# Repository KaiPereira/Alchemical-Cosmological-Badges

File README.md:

# Alchemical-Cosmological Badges

These are alchemical-cosmological PCB hackathon badges I designed in a day for the Fallout hackathon in Shenzhen, China. It's 3 PCB's stacked on-top of each other using testpoints and it's powered by the 10 cent, CH32V003 MCU, with WS2812B neopixels.

## PCB Design

There's 2 different PCB's: the outer ring and the inner sun. The 2 outer rings are soldered onto the testpoints of the inner one with the second outer ring rotated 180 degree's to look more 3D.

The rings have exposed soldermask so that the neopixels can shine through, and you actually only need to solder neopixels onto one ring to get the effect.

There's also a battery connector on the top-left corner to attach a small battery with a voltage between 2.7V - 5V, and I'd just suggest a small LiPo, that can potentially even slot in-between the boards.

I'd also suggest putting a hole for your lanyard, because currently I just have a string wrapped around the board which looks cool, but isn't the most convenient for assembly. 

## Manufacturing

Each full badge costs about $10 at MOQ, but I'm sure you could get that down to under $3 if you create quite a few at once.

If you want to manufacture the boards, all of their production and development files are in their relative folder. I'd suggest getting the boards from JLCPCB with ENIG and a stencil for the inner board, and then buying the components from LCSC and hand soldering. 

All the design files are also open-source if you want to make modifications so that they're unique to you, so just go crazy!!

These boards were designed really fast and made to be really cheap because of a limited budget, so produce them at your own discretion.

## Firmware

These boards use the CH32V003 and program over SWIO using the header pins in the middle of the board. You'll want to program the boards using either a WCH-LinkE or PicoRVD which is what I used and what you'll find in the firmware folder.

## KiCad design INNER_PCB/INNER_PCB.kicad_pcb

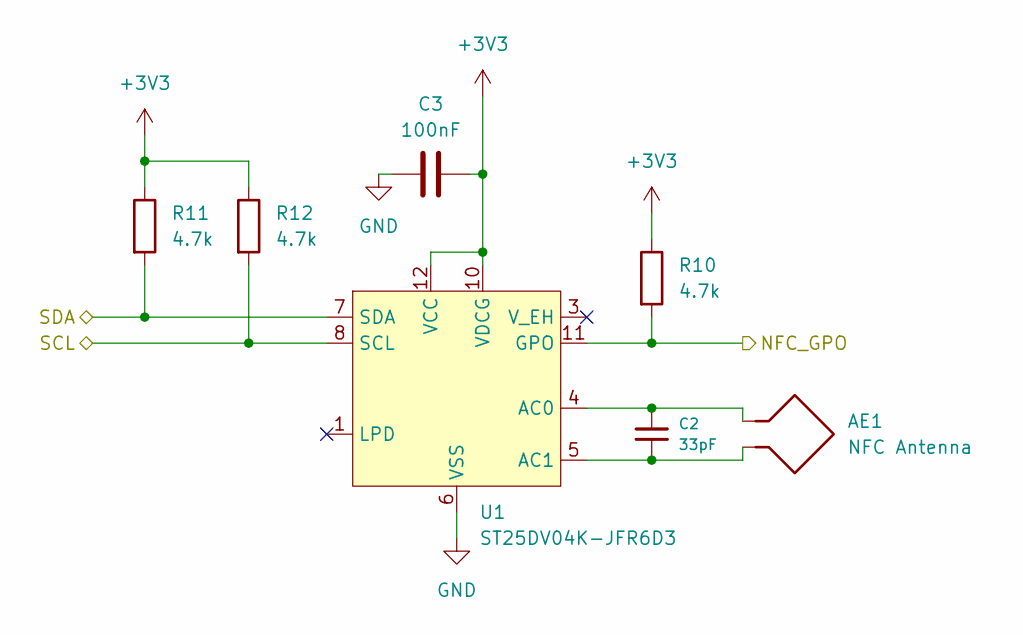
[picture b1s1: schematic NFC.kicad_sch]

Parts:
AE1: NFC Antenna; NFC_Coil_Round_D20mm_17T
C2: 33pF; C_0603_1608Metric; JLCPCB Part # C1663
C3: 100nF; C_0603_1608Metric; JLCPCB Part # C14663
R10, R11, R12: 4.7k; R_0603_1608Metric; JLCPCB Part # C23162
U1: ST25DV04K-JFR6D3; ST_UFDFPN-12-1EP_3x3mm_P0.5mm_EP1.4x2.55mm; JLCPCB Part # C2654815

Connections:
+3V3: C3.2, R10.1, R11.1, R12.1, U1.10 (VDCG), U1.12 (VCC); also elsewhere on the board
/MCU, Programming and Battery/NFC_GPO: R10.2, U1.11 (GPO); also elsewhere on the board
/MCU, Programming and Battery/SCL: R12.2, U1.8 (SCL); also elsewhere on the board
/MCU, Programming and Battery/SDA: R11.2, U1.7 (SDA); also elsewhere on the board
GND: C3.1, U1.6 (VSS); also elsewhere on the board
unnamed: AE1.1, C2.1, U1.4 (AC0)
unnamed: AE1.2, C2.2, U1.5 (AC1)

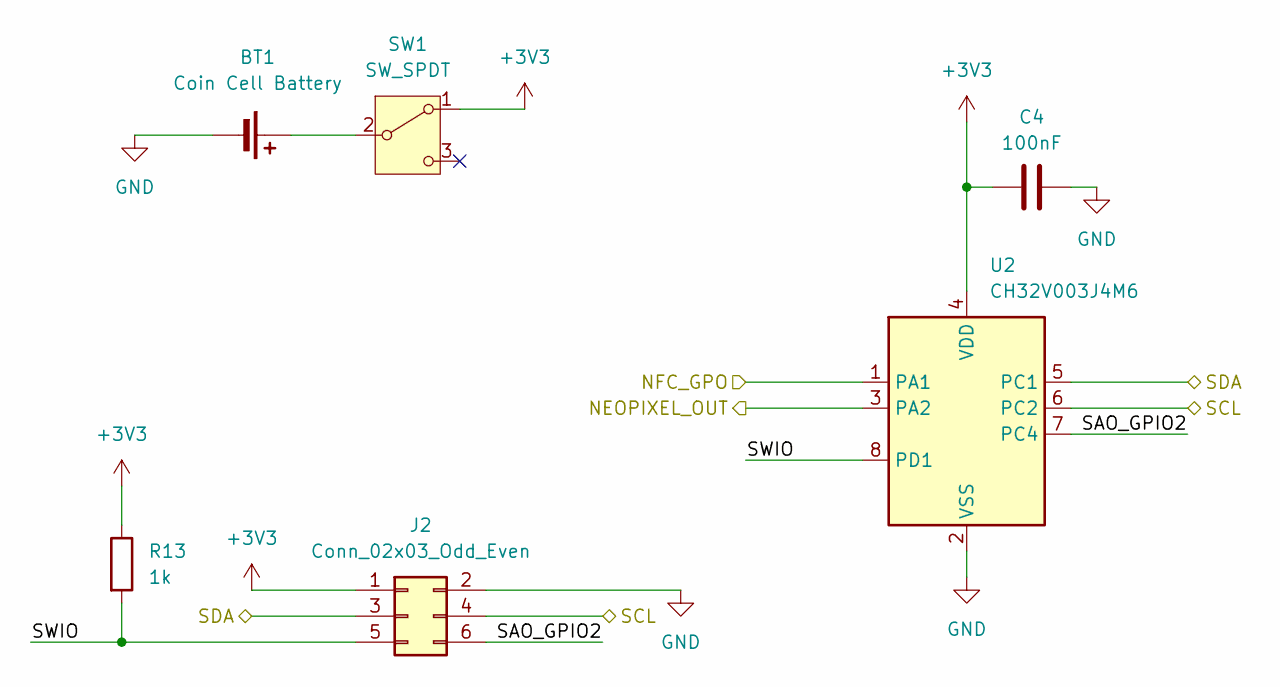
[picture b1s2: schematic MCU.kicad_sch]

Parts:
BT1: Coin Cell Battery; BatteryHolder_Keystone_1058_1x2032; JLCPCB Part # C964769
C4: 100nF; C_0603_1608Metric; JLCPCB Part # C14663
J2: Conn_02x03_Odd_Even; PinHeader_2x03_P2.54mm_Vertical_SMD; JLCPCB Part # C192301
R13: 1k; R_0603_1608Metric; JLCPCB Part # C21190
SW1: SW_SPDT; SS-3292S-L1-B; JLCPCB Part # C397350
U2: CH32V003J4M6; SSOP-8_3.9x5.05mm_P1.27mm; LCSC Part # C5346354

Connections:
+3V3: C4.1, J2.1, R13.1, SW1.1 (A), U2.4 (VDD); also elsewhere on the board
/Connecting Solder Points/NEOPIXEL_IN: U2.3 (PA2); also elsewhere on the board
/MCU, Programming and Battery/NFC_GPO: U2.1 (PA1); also elsewhere on the board
/MCU, Programming and Battery/SAO_GPIO2: J2.6, U2.7 (PC4)
/MCU, Programming and Battery/SCL: J2.4, U2.6 (PC2); also elsewhere on the board
/MCU, Programming and Battery/SDA: J2.3, U2.5 (PC1); also elsewhere on the board
/MCU, Programming and Battery/SWIO: J2.5, R13.2, U2.8 (PD1)
GND: BT1.2 (-), C4.2, J2.2, U2.2 (VSS); also elsewhere on the board
unnamed: BT1.1 (+), SW1.2 (B)

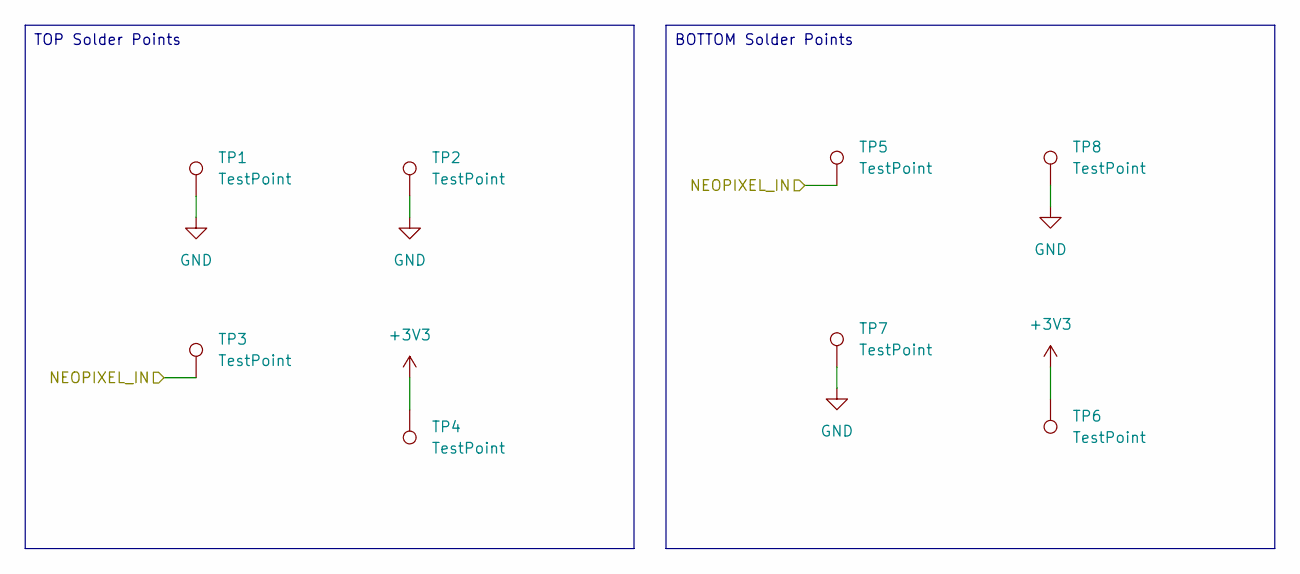
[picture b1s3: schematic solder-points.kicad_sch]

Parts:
TP1, TP2, TP3, TP4, TP5, TP6, TP7, TP8: TestPoint; TestPoint_Pad_3.0x3.0mm

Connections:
+3V3: TP4.1 (1_1), TP6.1 (1_1); also elsewhere on the board
/Connecting Solder Points/NEOPIXEL_IN: TP3.1 (1_1), TP5.1 (1_1); also elsewhere on the board
GND: TP1.1 (1_1), TP2.1 (1_1), TP7.1 (1_1), TP8.1 (1_1); also elsewhere on the board

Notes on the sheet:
TOP Solder Points
BOTTOM Solder Points

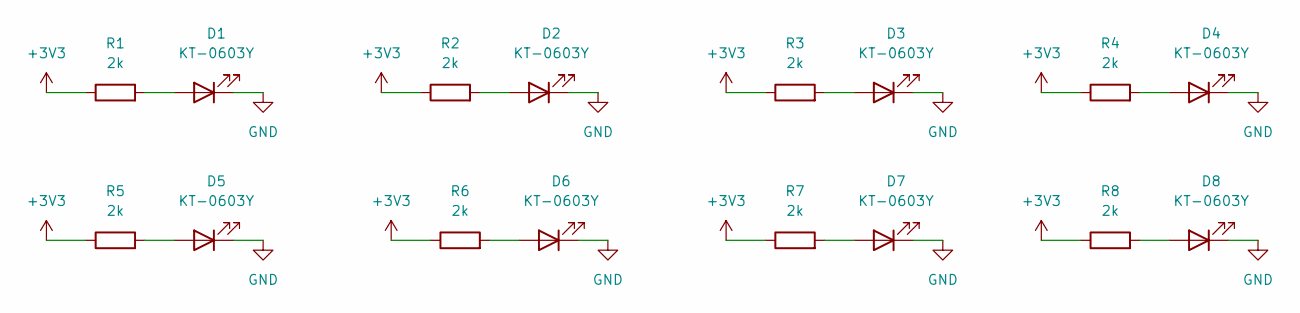
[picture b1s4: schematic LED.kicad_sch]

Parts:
D1, D2, D3, D4, D5, D6, D7, D8: KT-0603Y; LED_0603_1608Metric; JLCPCB Part # C2287
R1, R2, R3, R4, R5, R6, R7, R8: 2k; R_0402_1005Metric; JLCPCB Part # C4109

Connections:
+3V3: R1.1, R2.1, R3.1, R4.1, R5.1, R6.1, R7.1, R8.1; also elsewhere on the board
GND: D1.1 (K), D2.1 (K), D3.1 (K), D4.1 (K), D5.1 (K), D6.1 (K), D7.1 (K), D8.1 (K); also elsewhere on the board
unnamed: D1.2 (A), R1.2
unnamed: D2.2 (A), R2.2
unnamed: D3.2 (A), R3.2
unnamed: D4.2 (A), R4.2
unnamed: D5.2 (A), R5.2
unnamed: D6.2 (A), R6.2
unnamed: D7.2 (A), R7.2
unnamed: D8.2 (A), R8.2

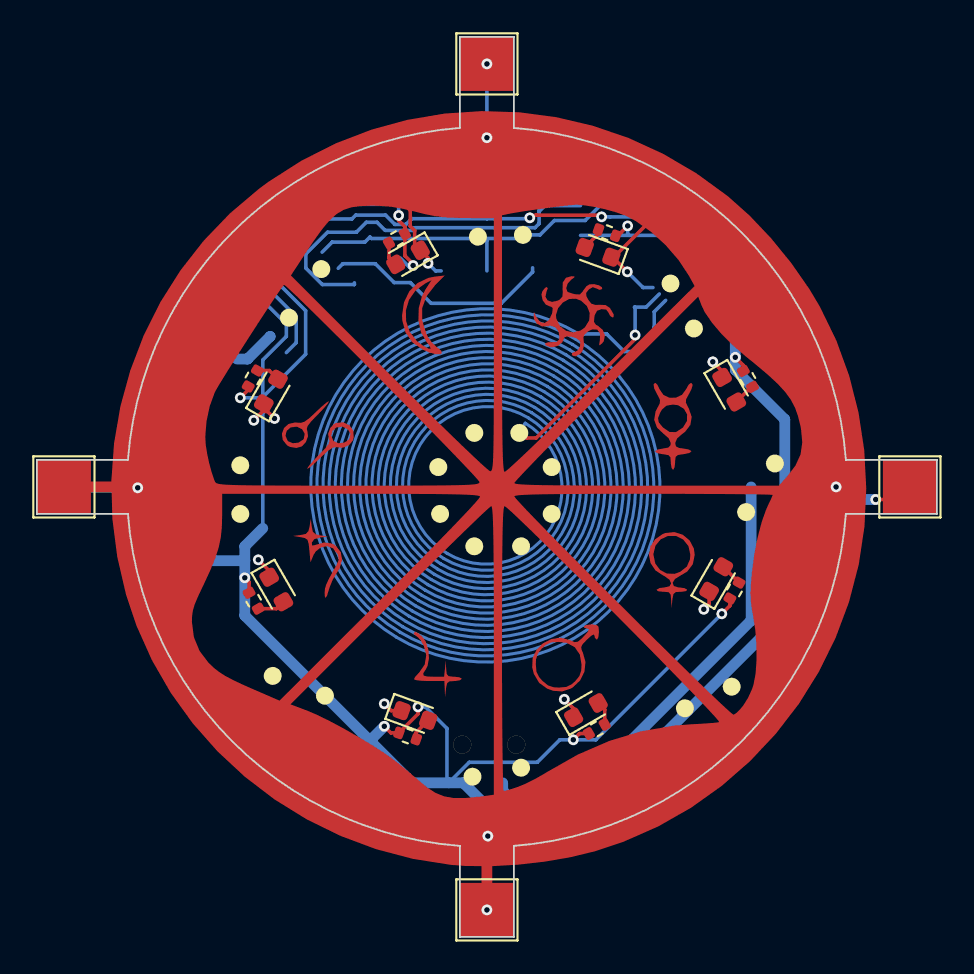
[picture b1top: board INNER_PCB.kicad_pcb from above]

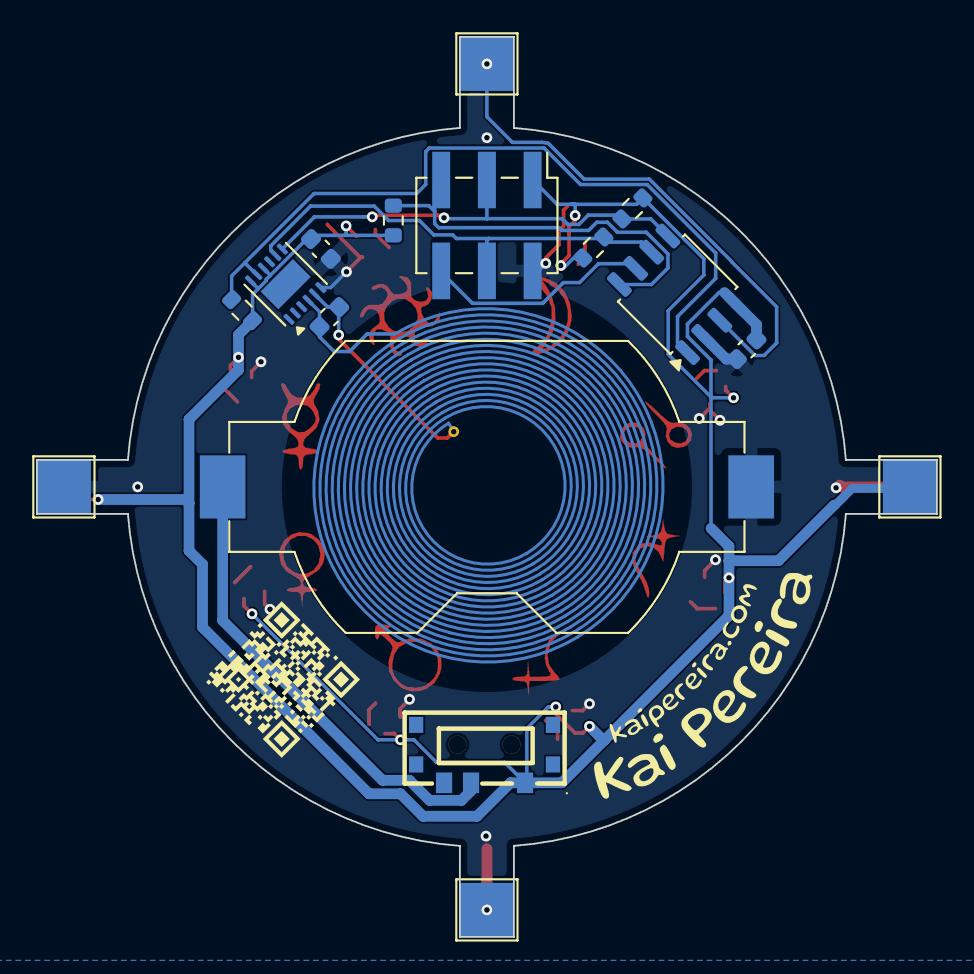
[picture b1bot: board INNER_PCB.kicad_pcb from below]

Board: 2 copper layers, 50.0 x 50.0 mm, 37 parts (17 on the bottom side), 19 nets.

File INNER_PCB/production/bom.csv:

Designator,Footprint,Quantity,Value,LCSC Part #
AE1,NFC_Coil_Round_D20mm_17T,1,NFC Antenna,
BT1,BatteryHolder_Keystone_1058_1x2032,1,Coin Cell Battery,C964769
C2,0603,1,33pF,C1663
"C3, C4",0603,2,100nF,C14663
"D1, D2, D3, D4, D5, D6, D7, D8",0603,8,KT-0603Y,C2287
J2,PinHeader_2x03_P2.54mm_Vertical_SMD,1,Conn_02x03_Odd_Even,C192301
"R1, R2, R3, R4, R5, R6, R7, R8",0402,8,2k,C4109
"R10, R11, R12",0603,3,4.7k,C23162
R13,0603,1,1k,C21190
SW1,SS-3292S-L1-B,1,SW_SPDT,C397350
"TP1, TP2, TP3, TP4, TP5, TP6, TP7, TP8",TestPoint_Pad_3.0x3.0mm,8,TestPoint,
U1,ST_UFDFPN-12-1EP_3x3mm_P0.5mm_EP1.4x2.55mm,1,ST25DV04K-JFR6D3,C2654815
U2,SSOP-8_3.9x5.05mm_P1.27mm,1,CH32V003J4M6,C5346354

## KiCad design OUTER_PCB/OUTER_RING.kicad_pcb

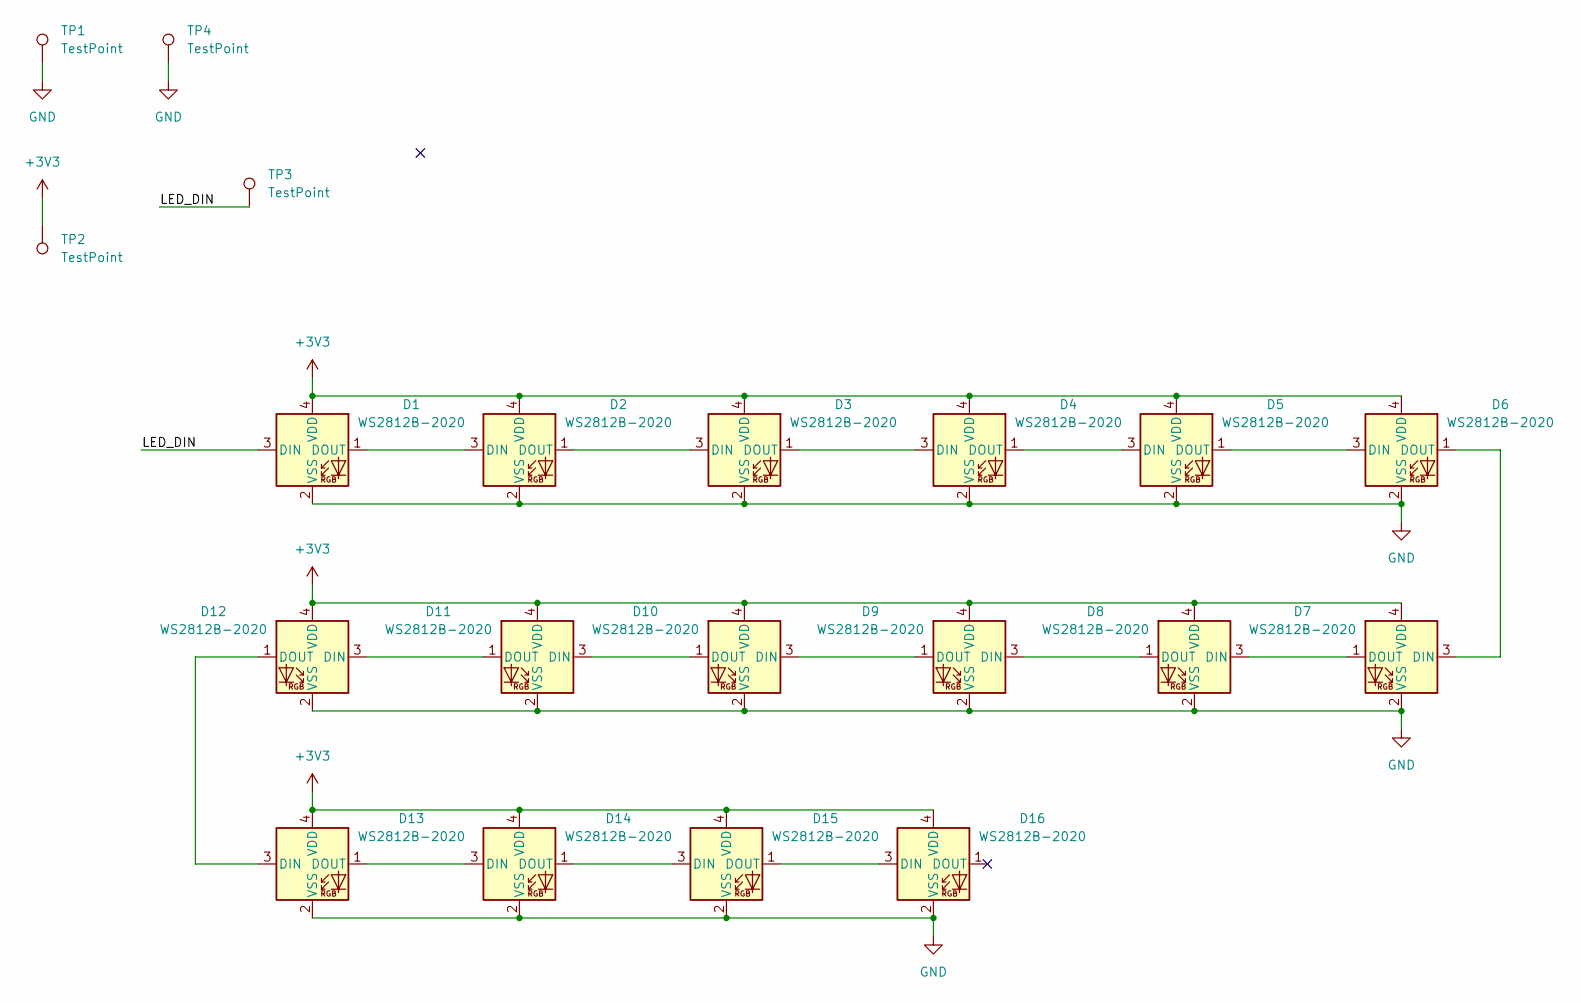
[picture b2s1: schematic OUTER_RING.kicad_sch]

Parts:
D1, D2, D3, D4, D5, D6, D7, D8, D9, D10, D11, D12, D13, D14, D15, D16: WS2812B-2020; LED_WS2812B-2020_PLCC4_2.0x2.0mm; JLCPCB Part # C52917434
TP1, TP2, TP3, TP4: TestPoint; TestPoint_Pad_4.0x4.0mm

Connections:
+3V3: D1.4 (VDD), D2.4 (VDD), D3.4 (VDD), D4.4 (VDD), D5.4 (VDD), D6.4 (VDD), D7.4 (VDD), D8.4 (VDD), D9.4 (VDD), D10.4 (VDD), D11.4 (VDD), D12.4 (VDD), D13.4 (VDD), D14.4 (VDD), D15.4 (VDD), D16.4 (VDD), TP2.1 (1_1)
/LED_DIN: D1.3 (DIN), TP3.1 (1_1)
GND: D1.2 (VSS), D2.2 (VSS), D3.2 (VSS), D4.2 (VSS), D5.2 (VSS), D6.2 (VSS), D7.2 (VSS), D8.2 (VSS), D9.2 (VSS), D10.2 (VSS), D11.2 (VSS), D12.2 (VSS), D13.2 (VSS), D14.2 (VSS), D15.2 (VSS), D16.2 (VSS), TP1.1 (1_1), TP4.1 (1_1)
unnamed: D1.1 (DOUT), D2.3 (DIN)
unnamed: D2.1 (DOUT), D3.3 (DIN)
unnamed: D3.1 (DOUT), D4.3 (DIN)
unnamed: D4.1 (DOUT), D5.3 (DIN)
unnamed: D5.1 (DOUT), D6.3 (DIN)
unnamed: D6.1 (DOUT), D7.3 (DIN)
unnamed: D7.1 (DOUT), D8.3 (DIN)
unnamed: D8.1 (DOUT), D9.3 (DIN)
unnamed: D9.1 (DOUT), D10.3 (DIN)
unnamed: D10.1 (DOUT), D11.3 (DIN)
unnamed: D11.1 (DOUT), D12.3 (DIN)
unnamed: D12.1 (DOUT), D13.3 (DIN)
unnamed: D13.1 (DOUT), D14.3 (DIN)
unnamed: D14.1 (DOUT), D15.3 (DIN)
unnamed: D15.1 (DOUT), D16.3 (DIN)

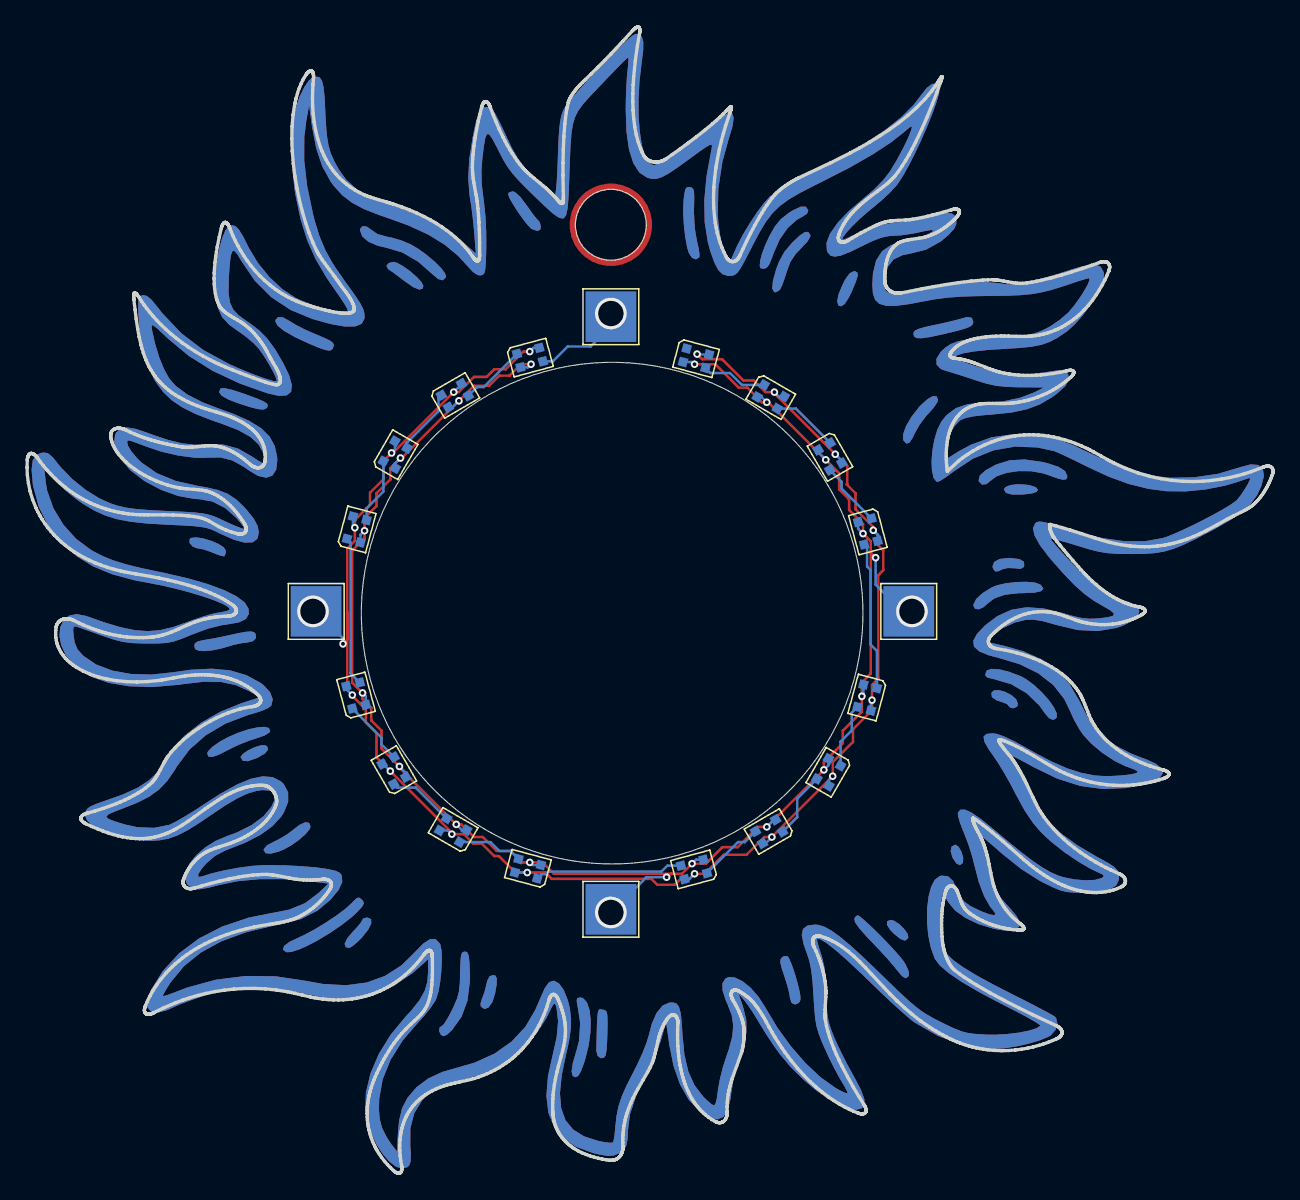
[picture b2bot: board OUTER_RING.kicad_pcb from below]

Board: 2 copper layers, 98.3 x 90.4 mm, 20 parts (20 on the bottom side), 18 nets.

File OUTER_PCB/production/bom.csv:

Designator,Footprint,Quantity,Value,LCSC Part #
"D1, D10, D11, D12, D13, D14, D15, D16, D2, D3, D4, D5, D6, D7, D8, D9",LED_WS2812B-2020_PLCC4_2.0x2.0mm,16,WS2812B-2020,C52917434
"TP1, TP2, TP3, TP4",TestPoint_Pad_4.0x4.0mm,4,TestPoint,
